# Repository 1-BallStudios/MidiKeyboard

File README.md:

# MidiKeyboard
Ok yeah I'm still not sure what I should put in the README's so It'll stay as a placeholder until I want to change it.
This is a custom MIDI Keyboard with switches, sliders, rotary encoders, neopixels and capacitive touch.
I think it turned out pretty well.

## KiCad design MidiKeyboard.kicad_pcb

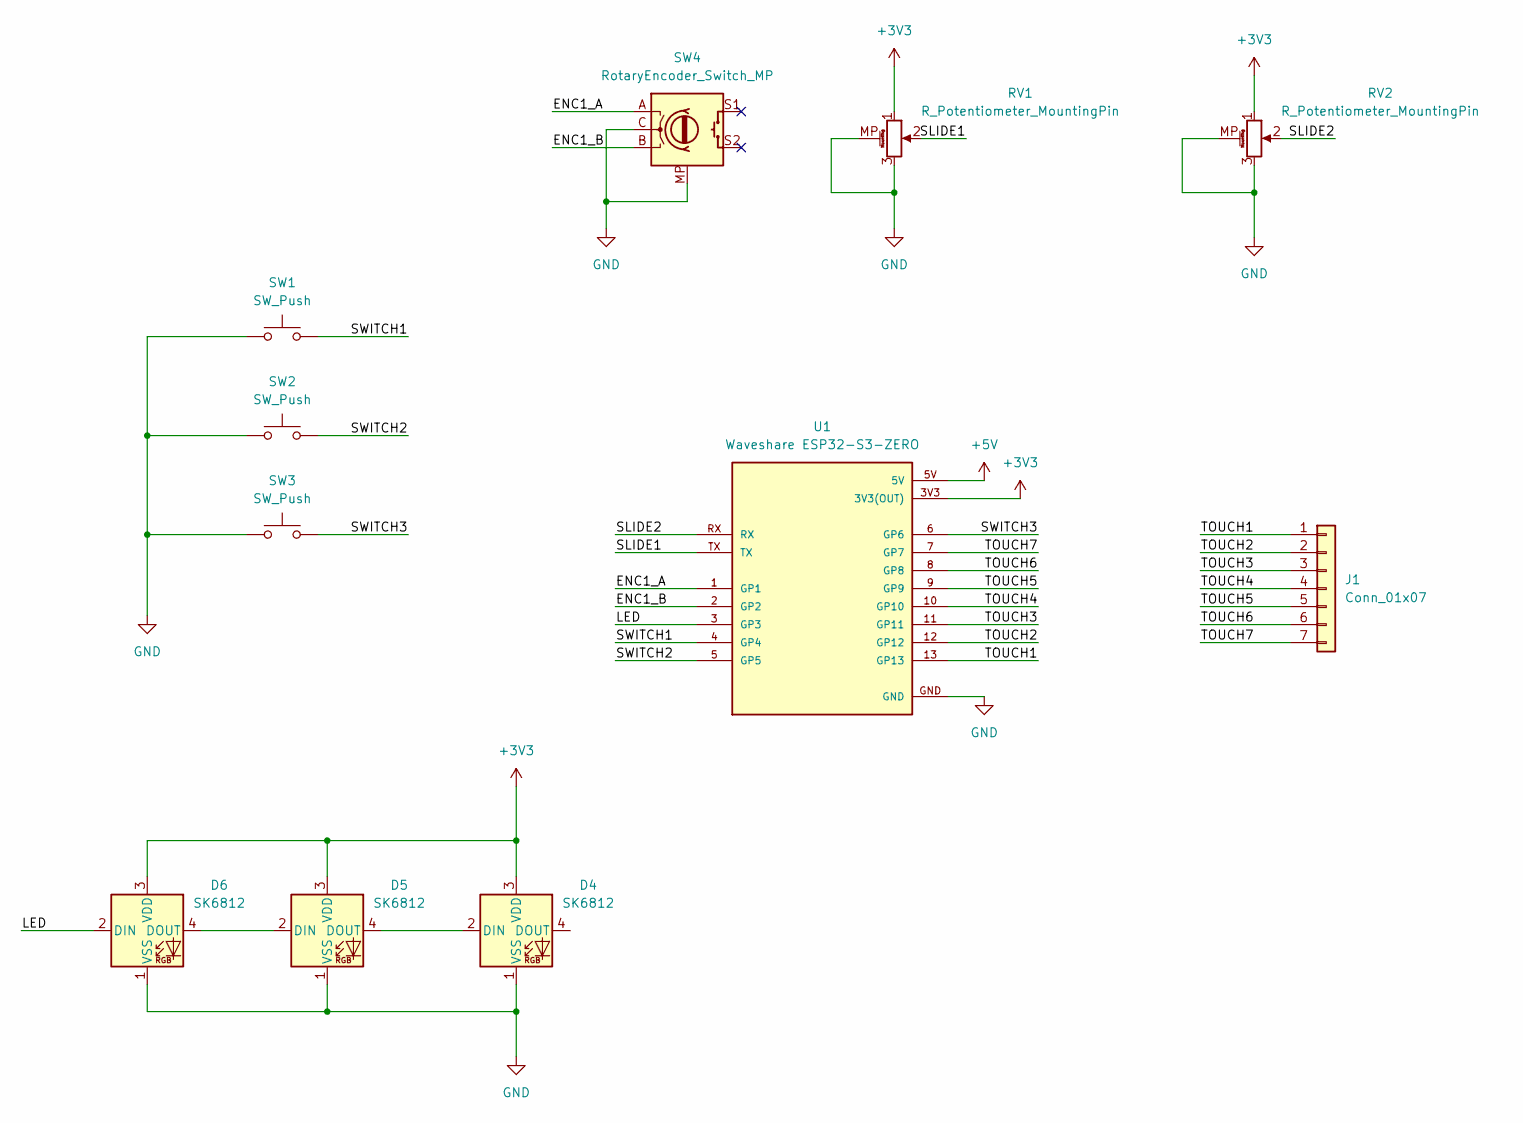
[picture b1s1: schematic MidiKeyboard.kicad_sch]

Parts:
D4, D5, D6: SK6812; LED_SK6812_PLCC4_5.0x5.0mm_P3.2mm
J1: Conn_01x07; Capacitive Keys
RV1, RV2: R_Potentiometer_MountingPin; Potentiometer_Bourns_PTA1543_Single_Slide
SW1, SW2, SW3: SW_Push; Kailh Choc Low-Profile Switches
SW4: RotaryEncoder_Switch_MP; RotaryEncoder_Alps_EC11E-Switch_Vertical_H20mm
U1: Waveshare ESP32-S3-ZERO; Waveshare ESP32-S3-Zero; PARTREV NA

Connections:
+3V3: D4.3 (VDD), D5.3 (VDD), D6.3 (VDD), RV1.1, RV2.1, U1.3V3 (3V3(OUT))
+5V: U1.5V
/ENC1_A: SW4.A, U1.1 (GP1)
/ENC1_B: SW4.B, U1.2 (GP2)
/LED: D6.2 (DIN), U1.3 (GP3)
/SLIDE1: RV1.2, U1.TX
/SLIDE2: RV2.2, U1.RX
/SWITCH1: SW1.2, U1.4 (GP4)
/SWITCH2: SW2.2, U1.5 (GP5)
/SWITCH3: SW3.2, U1.6 (GP6)
/TOUCH1: J1.1, U1.13 (GP13)
/TOUCH2: J1.2, U1.12 (GP12)
/TOUCH3: J1.3, U1.11 (GP11)
/TOUCH4: J1.4, U1.10 (GP10)
/TOUCH5: J1.5, U1.9 (GP9)
/TOUCH6: J1.6, U1.8 (GP8)
/TOUCH7: J1.7, U1.7 (GP7)
GND: D4.1 (VSS), D5.1 (VSS), D6.1 (VSS), RV1.3, RV1.MP (MountPin), RV2.3, RV2.MP (MountPin), SW1.1, SW2.1, SW3.1, SW4.C, SW4.MP, U1.GND
unnamed: D4.2 (DIN), D5.4 (DOUT)
unnamed: D5.2 (DIN), D6.4 (DOUT)

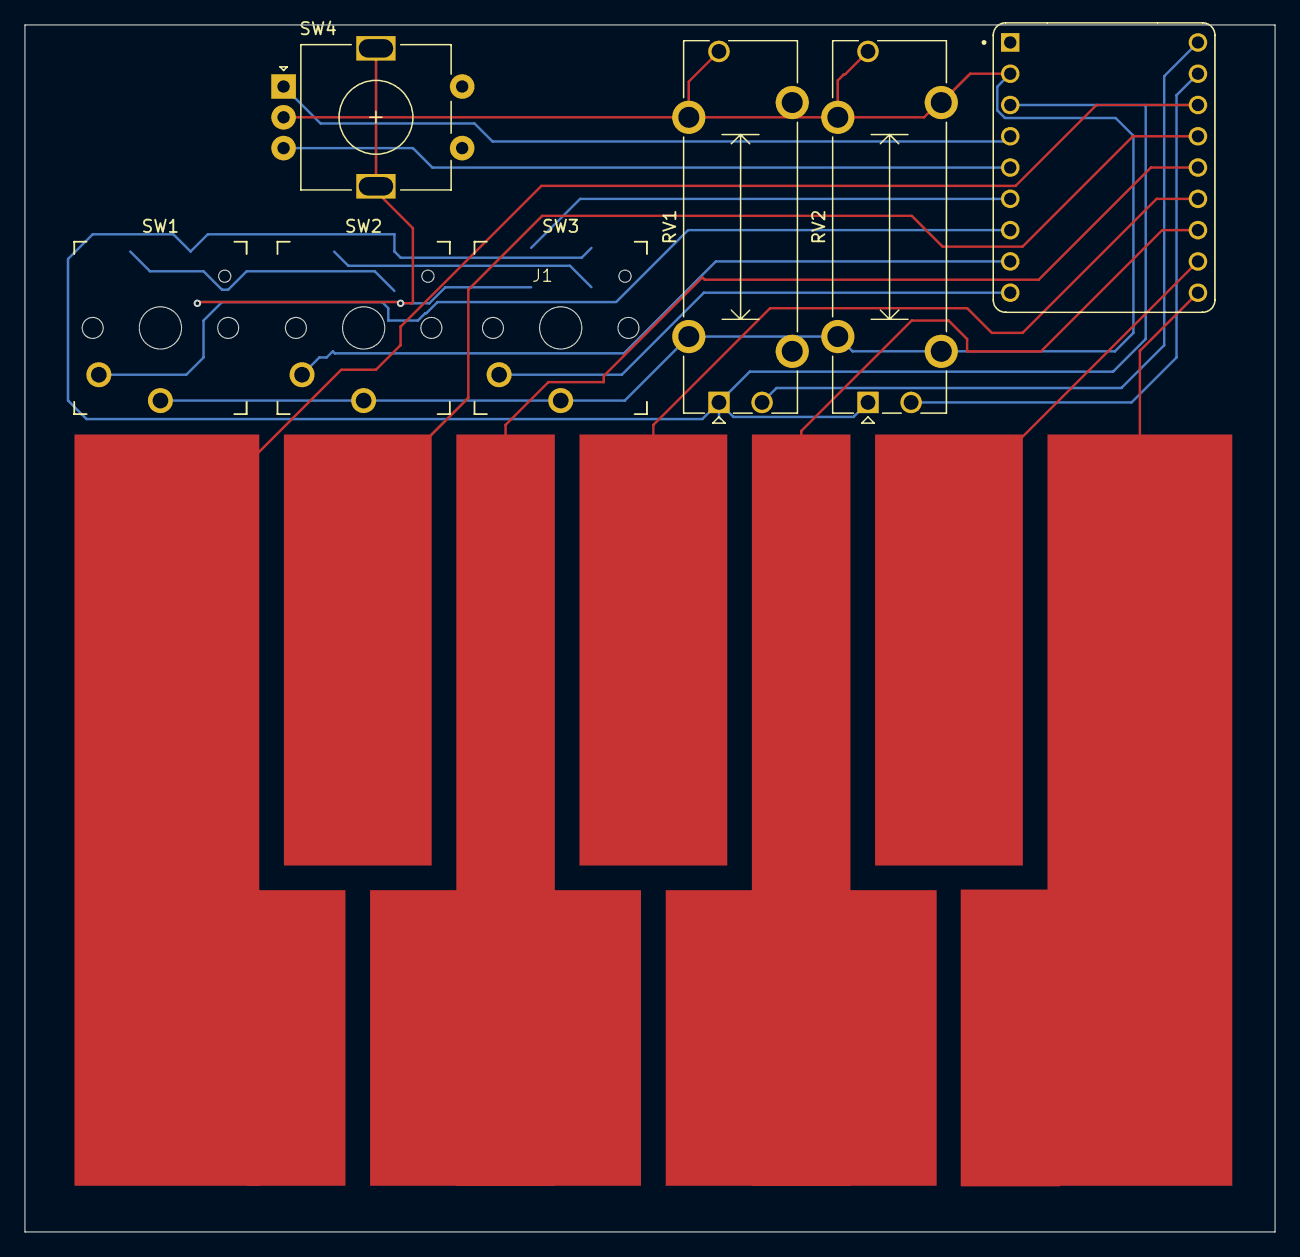
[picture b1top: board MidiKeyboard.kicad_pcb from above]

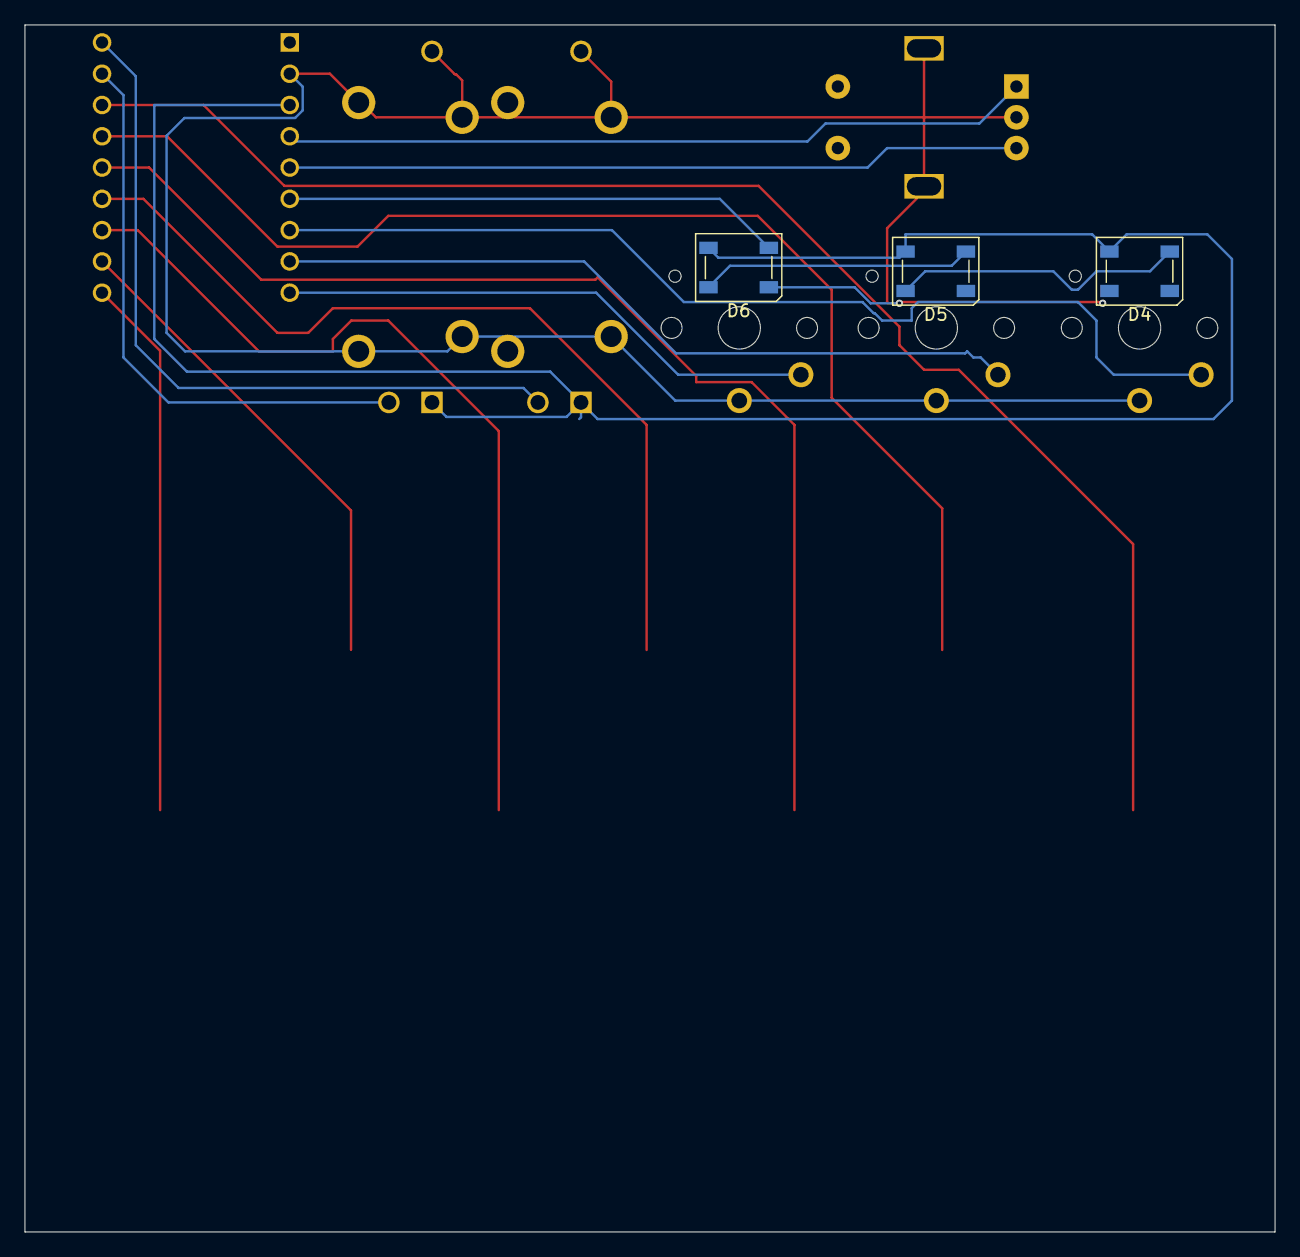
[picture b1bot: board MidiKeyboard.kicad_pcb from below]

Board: 2 copper layers, 101.5 x 98.0 mm, 11 parts (3 on the bottom side), 19 nets.

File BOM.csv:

Item,Qty,Supplier,Cost/item,Total Cost,link
SK6812,3,,$0.00,$0.00,
Conn_01x07,1,,$0.00,$0.00,
R_Potentiometer_MountingPin,2,,$0.00,$0.00,
SW_Push,3,,$0.00,$0.00,
RotaryEncoder_Switch_MP,1,,$0.00,$0.00,
Waveshare ESP32-S3-ZERO,1,,$0.00,$0.00,
Estimated total shipping,1,,,$0.00,
